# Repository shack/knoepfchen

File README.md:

# Knoepfchen

The unpronounceable PCB!

## Purpose

A small PCB with two debounced buttons, a debounced [SPDT](https://en.wikipedia.org/wiki/Switch#Contact_terminology) switch, and a [555](https://en.wikipedia.org/wiki/555_timer_IC) in astable configuration.

When experimenting with logic circuits, one often needs a switch or a button or a clock.
However, putting small debounce circuits on the breadboard over and over again is tedious.
Knoepfchen is a small PCB that you can just put on your breadboard and get two debounced buttons, a debounced switch, a 555 in astable mode, a two inverters with all relevant connectors available.

## Connectors

Knoepfchen has to rows of connectors:
The lower ones connect to the power rails of the breadboard.
The upper row can be plugged into the upper half of the breadboard and exposes all relevant connectors. These are from left to right:

| Number | Label | I/O | Description                                       |
| ------ | ----- | --- | ------------------------------------------------- |
| 1      | a     | I   | Input to an 74HCT14 inverter                      |
| 2      | ~a    | O   | Negation of a (output of inverter)                |
| 3      | b     | I   | Input to an 74HCT14 inverter                      |
| 4      | ~b    | O   | Negation of b (output of inverter)                |
| 5      | b1    | O   | Debounced button 1 (active high)                  |
| 6      | b2    | O   | Debounced button 2 (active high)                  |
| 7      | s     | O   | Position 1 of debounced SPDT switch               |
| 8      | DIS   | -   | Pin 7 of 555                                      |
| 9      | THR   | -   | Pin 6 of 555                                      |
| 10     | CLK   | O   | Pin 3 of 555                                      |

## Usage

- The buttons can be used for reset or a manual clock pulse.
- The RC network of the buttons also can also serve as a power-on reset circuit, providing a active-high RESET signal after ~40ms (see details below).
- The two inverter inputs can for example be used to create a active-low RESET signal and/or an inverted clock.
- If you don't need the 555, just leave pins 9-11 unconnected.
- If you don't need an inverter input, tie it low or high.
- All other pins don't need to be connected.

## Technical Details

- The switch debouncing circuit uses two inverter gates in a feedback configuration through a resistor (R5) as in The Art of Electronics, 3rd ed. Figure 10.52, page 730.
- The two buttons are identical and debounced using a standard RC circuit as in [this document](https://www.we-online.com/web/en/index.php/download/media/07_electronic_components/download_center_1/application_notes_berichte/sn015__contact_circuit_debounce_for_switches/SN015a_EN.pdf) but without the diode. Resistors R1 and R2 from the schematics are 1k and correspond to R1 in the document. Similarly, R3 and R4 are 10k and correspond to R2 in the document. C1 and C2 correspond to the capacitor and have 1µF each.
- C5 is a decoupling capacitor for the '14 chip and the 555.
- C4 connects to the CONTROL pin (pin 5) of the 555 and to GND.

## Configurations for the 555 in Astable Mode

Here, a brief summary of two standard configurations to get a clock signal out of the 555.

### The standard configuration
- Resistor R1 from Vcc to DIS
- Resistor R2 from DIS to THR
- Capacitor C from THR to GND

The frequency is then $\frac 1{\ln 2\cdot(R_1+2R_2)\cdot C}$ and the duty cycle is $\frac {R_1+R_2}{R_1+2R_2}$

### A 50% duty cycle configuration
- Resistor R from THR to CLK
- Capacitor C from THR to GND
- DIS not connected
- Duty cycle: 50%
- Note that you cannot put a resistive load to CLK without changing the duty cycle. 

The frequency is then $\frac 1{2\ln 2\cdot RC}$ 

More details on both configurations and more can be found for example [here](https://www.electronics-tutorials.ws/waveforms/555-circuits-part-1.html).

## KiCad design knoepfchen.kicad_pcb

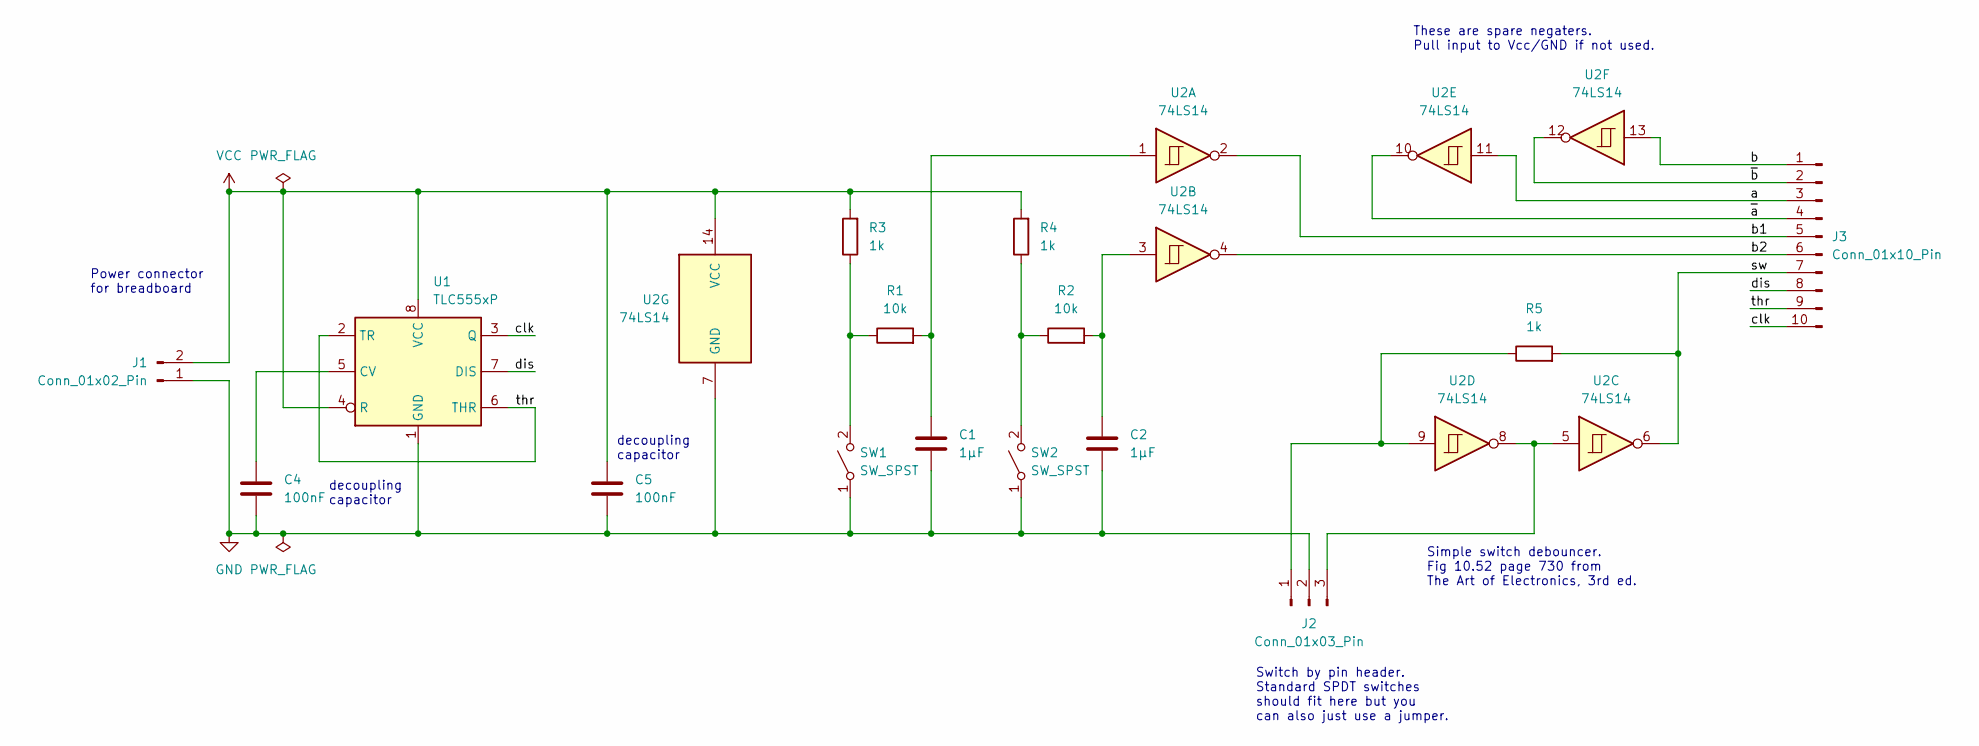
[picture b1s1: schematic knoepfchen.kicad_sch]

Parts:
C1, C2: 1µF; CP_Radial_D4.0mm_P1.50mm
C4, C5: 100nF; C_Disc_D5.0mm_W2.5mm_P5.00mm
J1: Conn_01x02_Pin; PinHeader_1x02_P2.54mm_Vertical
J2: Conn_01x03_Pin; PinHeader_1x03_P2.54mm_Vertical
J3: Conn_01x10_Pin; PinHeader_1x10_P2.54mm_Vertical
R1, R2: 10k; R_Axial_DIN0207_L6.3mm_D2.5mm_P2.54mm_Vertical
R3, R4, R5: 1k; R_Axial_DIN0207_L6.3mm_D2.5mm_P2.54mm_Vertical
SW1, SW2: SW_SPST; SW_PUSH_6mm
U1: TLC555xP; DIP-8_W7.62mm
U2: 74LS14; DIP-14_W7.62mm

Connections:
/a: J3.3, U2.11
/b: J3.1, U2.13
/b1: J3.5, U2.2
/b2: J3.6, U2.4
/clk: J3.10, U1.3 (Q)
/dis: J3.8, U1.7 (DIS)
/sw: J3.7, R5.2, U2.6
/thr: J3.9, U1.2 (TR), U1.6 (THR)
/~a: J3.4, U2.10
/~b: J3.2, U2.12
GND: C1.2, C2.2, C4.2, C5.2, J1.1, J2.2, SW1.1 (A), SW2.1 (A), U1.1 (GND), U2.7 (GND)
unnamed: C1.1, R1.2, U2.1
unnamed: C2.1, R2.2, U2.3
unnamed: J2.1, R5.1, U2.9
unnamed: J2.3, U2.5, U2.8
unnamed: R1.1, R3.1, SW1.2 (B)
unnamed: R2.1, R4.1, SW2.2 (B)
unnamed: C4.1, U1.5 (CV)
VCC: C5.1, J1.2, R3.2, R4.2, U1.4 (R), U1.8 (VCC), U2.14 (VCC)

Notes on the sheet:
decoupling capacitor
Power connector for breadboard
Simple switch debouncer. Fig 10.52 page 730 from The Art of Electronics, 3rd ed.
These are spare negaters. Pull input to Vcc/GND if not used.
Switch by pin header. Standard SPDT switches should fit here but you can also just use a jumper.

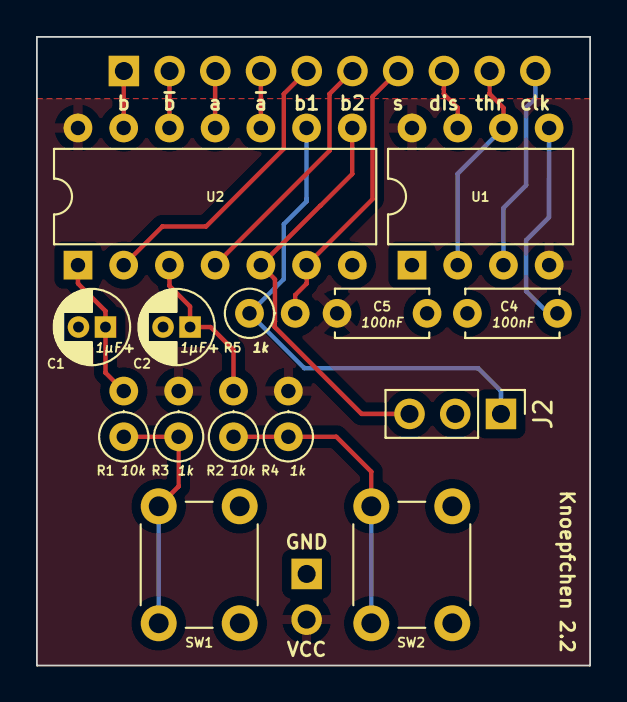
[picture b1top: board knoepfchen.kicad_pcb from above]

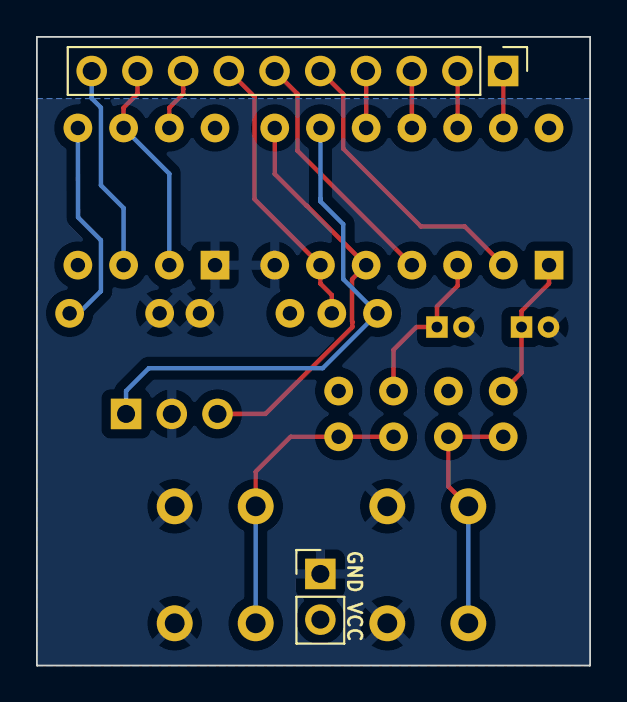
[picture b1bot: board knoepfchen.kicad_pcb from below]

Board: 2 copper layers, 30.7 x 34.9 mm, 16 parts (2 on the bottom side), 19 nets.

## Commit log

2022-04-21 removed old comment
2022-04-22 added math rendering
2022-04-25 changed cap value to match pcb
2022-04-28 revision 2.0
2022-04-28 added missing footprint
2022-04-28 typo
2022-04-28 fixed number
2022-04-28 fixed number again
2022-04-29 minor cosmetics
2022-04-30 simplified pcb layout
2022-05-01 smaller refinements
2022-05-02 updated image
2022-05-20 github md can render math now
2024-08-06 updated picture
2024-08-06 changed SPDT switch to standard jumper rail.
2025-03-03 updated kicad version
